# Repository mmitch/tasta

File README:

tasta - small USB keyboard
Copyright (C) 2015 by  Christian Garbs <mitch@cgarbs.de>
Licensed under GNU GPL v2 or v3

Project homepage:
-----------------
https://github.com/mmitch/tasta

Description:
------------
tasta a small USB HID keyboard with just two keys and the
corresponding code to program the ATtiny85.  This is my first
microcontroller/PCB project.  I developed it as a foot switch for
push-to-talk in TeamSpeak as I don't have any spare keys (or fingers)
during gaming.  I fiddled with this on and off over the course of two
years, now it should be ready to do something.

Hardware:
---------
The curcuit schematics and PCB layout are available in different
formats in the 'circuit' subdirectory.  They were created with KiCad,
so it's propably best to edit them with KiCad, too, if the need
arises.

There are some optional components in the layout:

 - You can omit the LED and R5 if you don't need it.

 - You can omit either key switch or the K1 connector as needed.  K1
   is used to provide key input from 'offboard', like the foot switch
   I use.

 - R4 is propably not needed.  In fact, I have never included it,
   neither in test runs nor in the final PCB.  But the docs say you
   should pull up your reset pin, so the possibility to insert the
   resistor is there if you should ever need it.  (I did include it
   'just in case' so I would not have to throw away the first PCB
   batch.)

Software:
---------
To build the software, go to the 'source' directory and just run
'make'.  A normal Atmel development environment is needed, so install
'avr-gcc' and friends.

To configure the software (to choose your own keybindings), edit
'main.c' and look for these two sections:
 - EDIT BELOW FOR YOUR OWN LED CONFIGURATION
 - EDIT BELOW FOR YOUR OWN KEY CONFIGURATION

Default configuration is:
 - key 1 = GUI left (Windows key -> modifier only)
 - key 2 = return
 - the LED is on if key 1 || key 2 is pressed

To flash the code to your ATtiny85, run 'make flash'.  The default
configuration uses avrdude with a 'usbasp' compatible programmer.
Edit the AVRDUDE_* variables in 'Makefile.orig' to change this.

Credits:
--------
PCB and basic code are heavily influenced from other projects, as you
can see in the repository log.  Other parts were rewritten, redone and
rearranged by myself.  Credits where credits are due:

 * VUSB project for USB on Atmel microcontrollers:
   http://www.obdev.at/vusb/

 * VUSB HIDKeys example project for a USB HID compliant keyboard:
   https://www.obdev.at/products/vusb/hidkeys.html

 * Information on running a VUSB project without a crystal taken from
   flipwork's 1-Key-keyboard:
   http://blog.flipwork.nl/?x=entry:entry081009-142605

 * better OSCCAL calibration routine taken from here:
   http://codeandlife.com/2012/02/22/v-usb-with-attiny45-attiny85-without-a-crystal/

 * My PCBs were printed at Hackvana.  I've never done this before and
   everything went right on the first try (well, on the second, I had
   one misnamed file in the rev_0x0002 export, but that's my fault):
   http://www.hackvana.com/

Licensing:
----------
The VUSB example projects are licensed under GPL 2 or GPL 3 (you can
choose).  The imported code from flipwork and codeandlife is based on
VUSB projects as well (HIDKeys/EasyLogger), so they're GPL 2/3, too.
My project thus is also GPL 2/3 and everybody's happy.

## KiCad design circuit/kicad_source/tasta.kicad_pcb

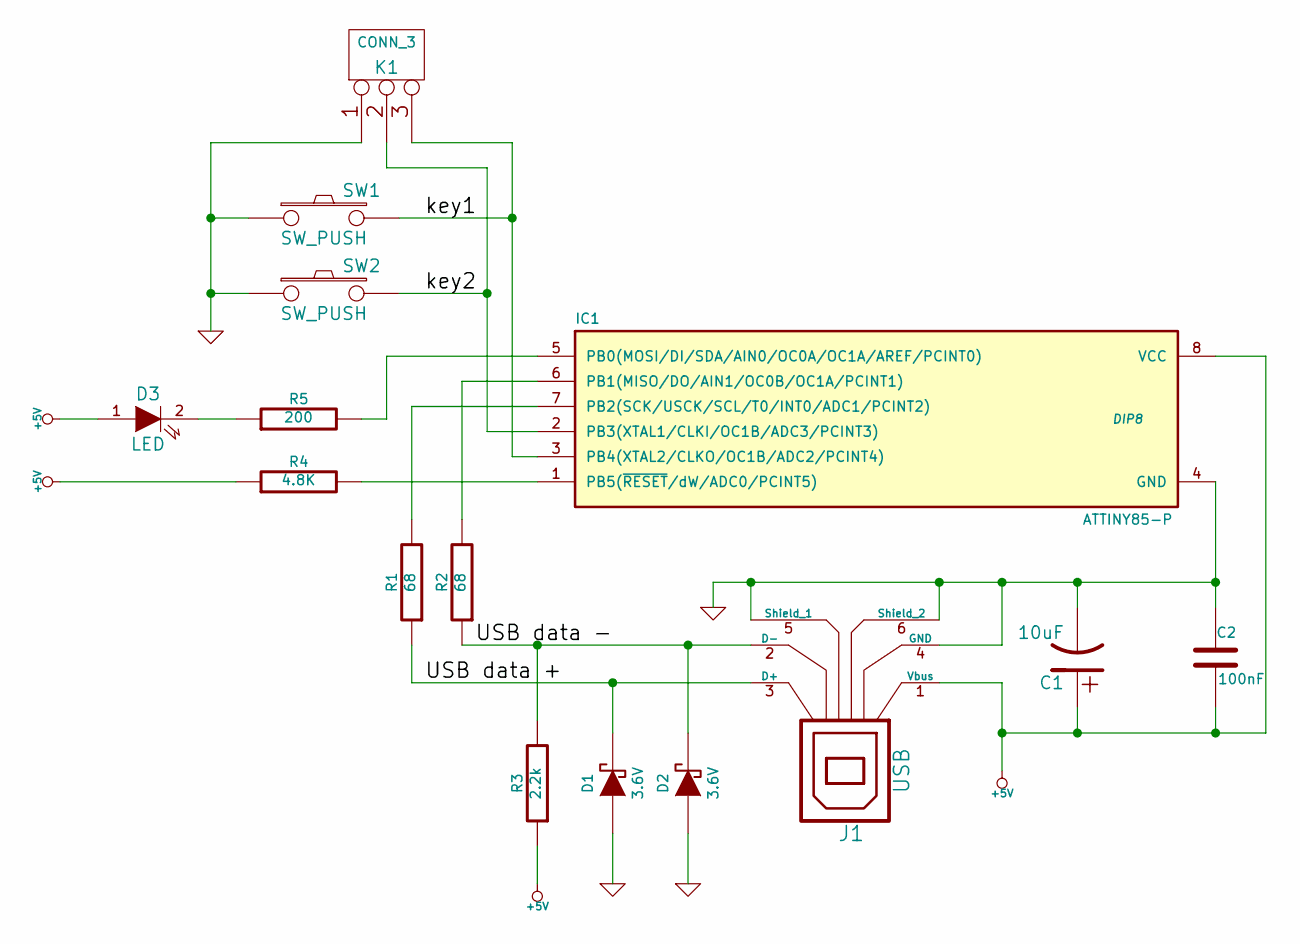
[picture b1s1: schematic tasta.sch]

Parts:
C1: 10uF
C2: 100nF
D1, D2: 3.6V
D3: LED
IC1: ATTINY85-P; DIP8
J1: USB
K1: CONN_3
R1, R2: 68
R3: 2.2k
R4: 4.8K
R5: 200
SW1, SW2: SW_PUSH

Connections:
+5V: C1.1, C2.2, D3.1 (A), IC1.8 (VCC), J1.1 (Vbus), R3.1, R4.1
/USB data +: D1.2 (K), J1.3 (D+), R1.1
/USB data -: D2.2 (K), J1.2 (D-), R2.1, R3.2
/key1: IC1.3 (PB4(XTAL2/CLKO/OC1B/ADC2/PCINT4)), K1.3, SW1.2
/key2: IC1.2 (PB3(XTAL1/CLKI/OC1B/ADC3/PCINT3)), K1.2 (PM), SW2.2
GND: C1.2, C2.1, D1.1 (A), D2.1 (A), IC1.4 (GND), J1.4 (GND), J1.5 (Shield_1), J1.6 (Shield_2), K1.1, SW1.1, SW2.1
unnamed: IC1.6 (PB1(MISO/DO/AIN1/OC0B/OC1A/PCINT1)), R2.2
unnamed: D3.2 (K), R5.1
unnamed: IC1.7 (PB2(SCK/USCK/SCL/T0/INT0/ADC1/PCINT2)), R1.2
unnamed: IC1.5 (PB0(MOSI/DI/SDA/AIN0/OC0A/OC1A/AREF/PCI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), R5.2
unnamed: IC1.1 (PB5(~RESET~/dW/ADC0/PCINT5)), R4.2

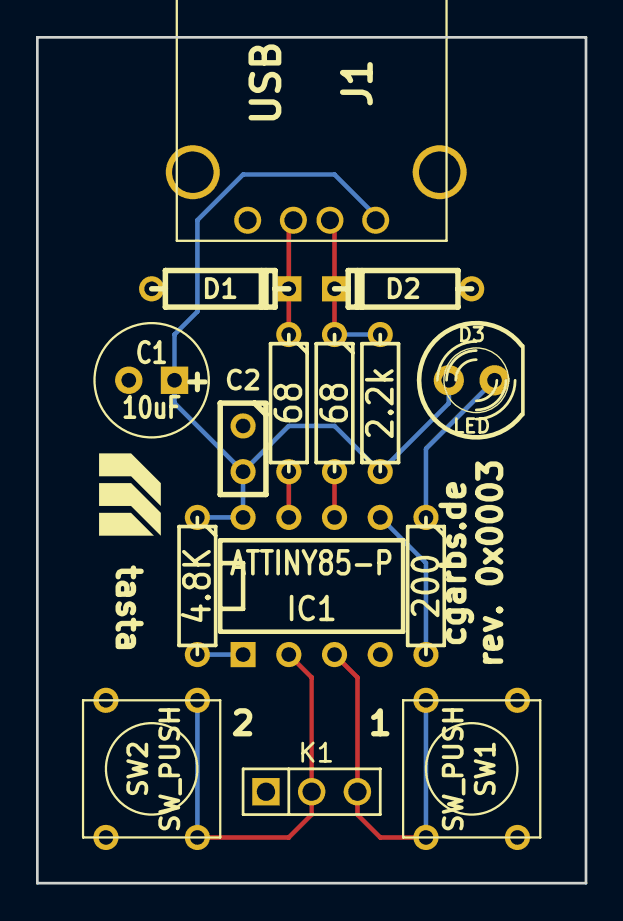
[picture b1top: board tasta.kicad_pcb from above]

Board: 2 copper layers, 30.5 x 47.0 mm, 15 parts (0 on the bottom side), 11 nets.

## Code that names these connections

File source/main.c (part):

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/* ----------------------- hardware I/O abstraction ------------------------ */

/* pin assignments:
PB0	LED (output, but acts as a sink: deactivate pullup = LED on)
PB1     USB data -
PB2     USB data +
PB3     button 2
PB4     button 1
PB5     reset (in hardware; unused here)
*/

#define BUTTON_PORT     PORTB       /* PORTx - register for buttons (pullups) */
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#define LED_PORT        PORTB       /* PORTx - register for LED (pullups) */
#define LED_DDR         DDRB        /* DDRx  - register for LED (set to output) */

#define BUTTON1_BIT     PB4         /* bit for button 1 in button register */
#define BUTTON2_BIT     PB3         /* bit for button 2 in button register */
#define LED_BIT         PB0         /* bit for LED in LED register */

#define KEY1            (1 << 0)    /* bitmask for key 1 */
#define KEY2            (1 << 1)    /* bitmask for key 2 */

/* LED is controlled via pull-up: no pullup = acts as sink = LED on */
#define LED_ON      (LED_PORT &= ~_BV(LED_BIT))
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
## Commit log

2015-03-16 initial schema and pcb import
2015-03-26 PCB layout: set stroke width of LED labels to 6mil
2015-03-26 remove unneeded and out of date autorouter file
2015-03-26 add .gitignore files
2015-03-26 prepare checkin of created Gerber files
    Gerber export via KiCad scripting might be possible, but for now
    just stick with a manual export
2015-03-26 fix renaming of files in KiCad export
    The Gerber mask files were missing and their filenames were confused
    with the copper layers'.
2015-03-26 add logo to PCB
2015-03-26 checkin exported Gerber files
2015-03-27 update logo on PCB
    handcrafted logo is better than Bitmap2Component conversion
2015-03-27 kicad_export: add check for revision on PCB before creating the ZIP
2015-04-21 fix frontsilk extension
    .gto, not .gbo
2015-04-21 update revision after frontsilk extension change
2015-07-16 import V-USB HIDKeys example project
    License.txt says it's GPL 2/3, so that's ok.
    Thanks go out to objective development for providing V-USB:
    http://www.obdev.at/vusb/
    The imported code was taken from here:
    https://www.obdev.at/downloads/vusb/HIDKeys.2012-12-08.tar.gz
2015-07-16 remove unneeded HIDKeys files
2015-07-16 reindent code
2015-07-16 switch to tasta hardware and define own keys
2015-07-16 reformat old code
2015-07-16 remove debugging
2015-07-16 more adjustments to tasta project
    - initialize the correct ports
    - switch timer timings to 16.5 MHz
    - do USB reset via device disconnect/reconnect
    This idea is taken from the flipwork 1-Key-Keyboard
    project at http://blog.flipwork.nl/?x=entry:entry081009-142605
    Source: http://blog.flipwork.nl/fp-content/attachs/1_key_keyboard.zip
2015-07-16 add timer calibration
    As tasta runs without external crystals on the internal clock of the
    ATtiny85, the timer has to be calibrated.
    This routine is again taken from the flipwork 1-Key-Keyboard
    project at http://blog.flipwork.nl/?x=entry:entry081009-142605
    Source: http://blog.flipwork.nl/fp-content/attachs/1_key_keyboard.zip
    The code distinguishes between USB resets (timing is recalculated and
2015-07-16 reformat code
2015-07-16 switch OSCCAL calibration routine
    Replace 1-Key-Keyboard's V-USB-based calibration routine by the one
    from here:
    http://codeandlife.com/2012/02/22/v-usb-with-attiny45-attiny85-without-a-crystal/
    This searches both regions 0..127 and 128..255, to which the original
    VUSB code said "this might be a good idea, so go and write your own
    calibration routine".
2015-07-16 fix typo
2015-07-16 switch to my own build system (read: different Makefile)
    see top of Makefile.orig for where this originates from...
2015-07-16 fix includes
2015-07-16 fix LED handling
    LED ON: output port has pullup removed and acts as a sink
    LED OFF: output port is pulled up, LED has +5V on both sides
2015-07-16 more #include fixes
2015-07-16 adjust usbconfig.h to tasta needs
2015-07-26 rewrite handling of keypresses
    - expand USB HID report to allow two keys at once
    - read multiple keypresses simultaneously (bit field)
    - dynamically create USB report (variable length/key count)
    Also mark code sections for user-defined keypress and LED handling.
2015-07-26 fix keypress events
    actually send the report that has been assembled :-)
2015-07-26 fix keypress detection
    d'oh: buttons are reversed - as always :-/
2015-07-26 fix errors in buildReport()
2015-07-26 add project info to schematics
2015-07-26 add schematics PDF export to repository
    No need to install KiCad to see what this is all about.
2015-07-26 check revision on schematics on export
    Also check the PDF, this needs the pdftotext utility.
    This should ensure that everything is up-to-date after any changes.
2015-07-26 clarify/add license
2015-07-26 add project README
2015-08-01 move key configuration examples inside the configuration section
2015-08-01 add 'hardware' and 'software' sections to README

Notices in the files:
source/main.c:
Copyright (C) 2015 Christian Garbs <mitch@cgarbs.de>
Copyright: (c) 2006 by OBJECTIVE DEVELOPMENT Software GmbH
License: GNU GPL v2  (or GNU GPL v3 as the complete License.txt says)
